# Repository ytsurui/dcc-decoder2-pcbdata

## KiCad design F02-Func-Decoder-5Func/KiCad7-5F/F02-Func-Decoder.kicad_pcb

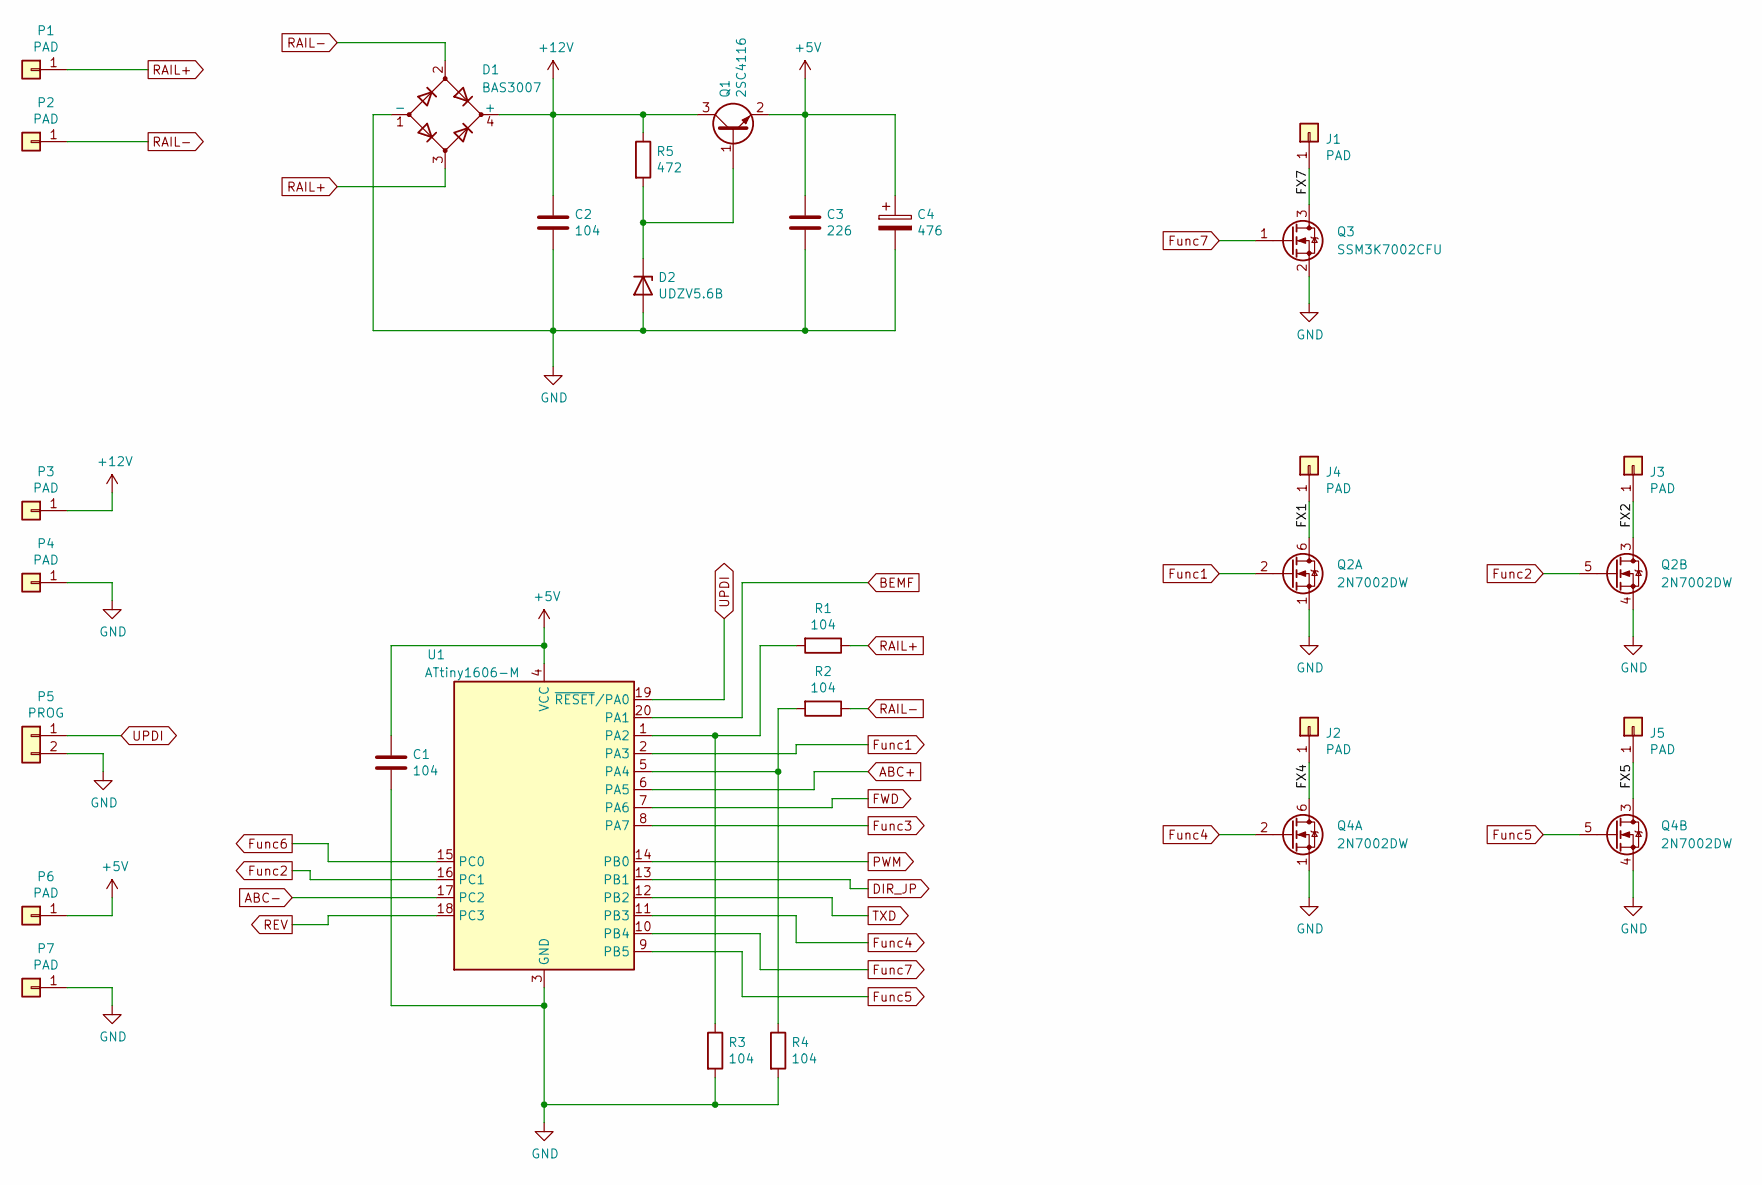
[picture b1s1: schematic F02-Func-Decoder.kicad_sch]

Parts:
C1, C2: 104; C_1005_v2
C3: 226; C_1608
C4: 476; CP_1608
D1: BAS3007; SOT-143
D2: UDZV5.6B; UMD2
J1, J2, J3, J4, J5: PAD; PAD_1.3x1.3_Hole0.9
P1, P2, P3, P4, P6, P7: PAD; PAD_1.3x1.3_Hole0.9
P5: PROG; PAD_PROG_2PIN_HOLE0.7
Q1: 2SC4116; SOT-23
Q2, Q4: 2N7002DW; SOT-363-nomark-v2
Q3: SSM3K7002CFU; SOT-23
R1, R2, R3, R4: 104; R_1608_20240411
R5: 472; R_1608_20240411
U1: ATtiny1606-M; VQFN-20-1EP_3x3mm_P0.4mm_EP1.7x1.7mm

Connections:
+5V: C1.1, C3.1, C4.1, P6.1, Q1.2 (E), U1.4 (VCC)
+12V: C2.1, D1.4 (+), P3.1, Q1.3 (C), R5.1
/FX1: J4.1, Q2.6 (D)
/FX2: J3.1, Q2.3 (D)
/FX4: J2.1, Q4.6 (D)
/FX5: J5.1, Q4.3 (D)
/FX7: J1.1, Q3.3 (D)
ABC+: U1.6 (PA5)
ABC-: U1.17 (PC2)
BEMF: U1.20 (PA1)
DIR_JP: U1.13 (PB1)
FWD: U1.7 (PA6)
Func1: Q2.2 (G), U1.2 (PA3)
Func2: Q2.5 (G), U1.16 (PC1)
Func3: U1.8 (PA7)
Func4: Q4.2 (G), U1.11 (PB3)
Func5: Q4.5 (G), U1.9 (PB5)
Func6: U1.15 (PC0)
Func7: Q3.1 (G), U1.10 (PB4)
GND: C1.2, C2.2, C3.2, C4.2, D1.1 (-), D2.2 (A), P4.1, P5.2, P7.1, Q2.1 (S), Q2.4 (S), Q3.2 (S), Q4.1 (S), Q4.4 (S), R3.2, R4.2, U1.3 (GND), U1.21 (GND)
unnamed: D2.1 (K), Q1.1 (B), R5.2
unnamed: R1.2, R3.1, U1.1 (PA2)
unnamed: R2.2, R4.1, U1.5 (PA4)
PWM: U1.14 (PB0)
RAIL+: D1.3, P1.1, R1.1
RAIL-: D1.2, P2.1, R2.1
REV: U1.18 (PC3)
TXD: U1.12 (PB2)
UPDI: P5.1, U1.19 (~RESET/PA0)

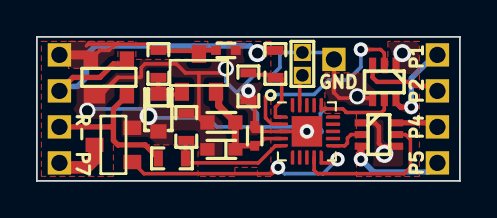
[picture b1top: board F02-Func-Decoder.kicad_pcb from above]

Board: 2 copper layers, 23.5 x 8.0 mm, 26 parts (0 on the bottom side), 19 nets.

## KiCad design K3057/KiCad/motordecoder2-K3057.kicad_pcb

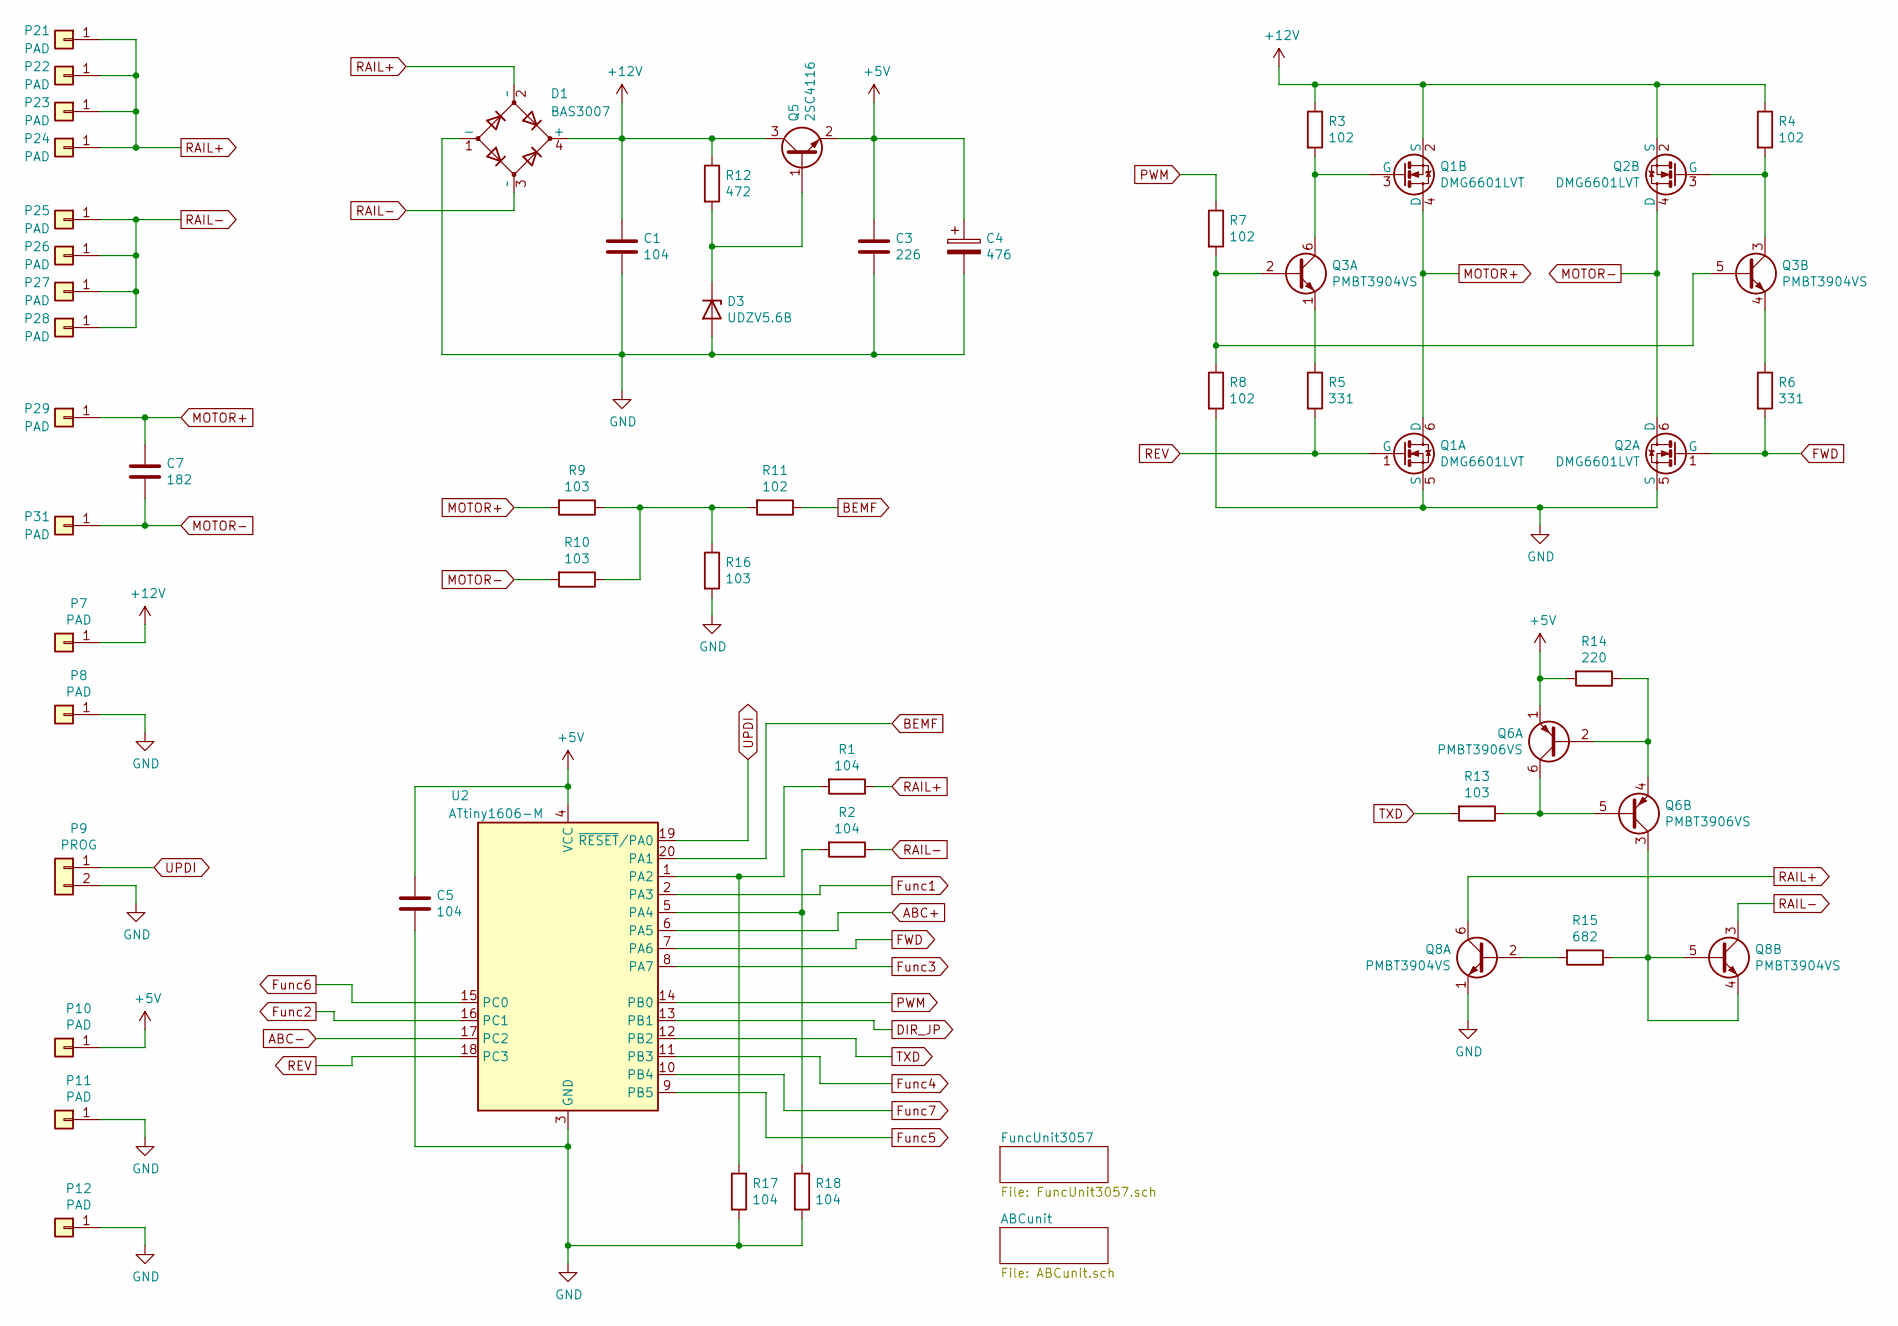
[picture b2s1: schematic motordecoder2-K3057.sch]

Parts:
C1, C5: 104; C_1005_v2
C3: 226; C_1608
C4: 476; CP_1608
C7: 182; C_1005_v2
D1: BAS3007; SOT-143
D3: UDZV5.6B; UMD2
P7: PAD; PAD_1.0x1.8_SMD
P8, P10: PAD; PAD_0.6x1.0_SMD
P9: PROG; PAD_PROG_2PIN_HOLE0.7
P11: PAD; PAD_0.5x1.2_SMD
P12: PAD; PAD_1.0x1.4_SMD
P21, P24, P25, P28, P29, P31: PAD; KATO_RAILPAD_3057_8mm
P22, P23, P26, P27: PAD; KATO_RAILPAD_3057_7mm
Q1, Q2: DMG6601LVT; SOT-23-6
Q3, Q8: PMBT3904VS; SOT-666-nomark
Q5: 2SC4116; SC-70_v2
Q6: PMBT3906VS; SOT-666-nomark
R1, R2, R17, R18: 104; R_1005
R3, R4: 102; R_1608_v2
R5, R6: 331; R_1608_v2
R7, R8, R11: 102; R_1005
R9, R10, R13, R16: 103; R_1005
R12: 472; R_1005
R14: 220; R_1608_v2
R15: 682; R_1005
U2: ATtiny1606-M; VQFN-20-1EP_3x3mm_P0.4mm_EP1.7x1.7mm

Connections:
+5V: C3.1, C4.1, C5.1, P10.1, Q5.2 (E), Q6.1 (E1), R14.2, U2.4 (VCC)
+12V: C1.1, D1.4 (+), P7.1, Q1.2 (S), Q2.2 (S), Q5.3 (C), R3.1, R4.1, R12.1; also elsewhere on the board
ABC+: U2.6 (PA5); also elsewhere on the board
ABC-: U2.17 (PC2); also elsewhere on the board
BEMF: R11.1, U2.20 (PA1)
DIR_JP: U2.13 (PB1); also elsewhere on the board
FWD: Q2.1 (G), R6.2, U2.7 (PA6)
Func1: U2.2 (PA3); also elsewhere on the board
Func2: U2.16 (PC1); also elsewhere on the board
Func3: U2.8 (PA7); also elsewhere on the board
Func4: U2.11 (PB3); also elsewhere on the board
Func5: U2.9 (PB5); also elsewhere on the board
Func6: U2.15 (PC0); also elsewhere on the board
Func7: U2.10 (PB4); also elsewhere on the board
GND: C1.2, C3.2, C4.2, C5.2, D1.1 (-), D3.2 (A), P8.1, P9.2, P11.1, P12.1, Q1.5 (S), Q2.5 (S), Q8.1 (E1), R8.2, R16.2, R17.2, R18.2, U2.3 (GND), U2.21 (GND); also elsewhere on the board
MOTOR+: C7.1, P29.1, Q1.4 (D), Q1.6 (D), R9.2
MOTOR-: C7.2, P31.1, Q2.4 (D), Q2.6 (D), R10.2
unnamed: D3.1 (K), Q5.1 (B), R12.2
unnamed: Q1.3 (G), Q3.6 (C1), R3.2
unnamed: Q2.3 (G), Q3.3 (C2), R4.2
unnamed: Q3.1 (E1), R5.1
unnamed: Q3.2 (B1), Q3.5 (B2), R7.2, R8.1
unnamed: Q3.4 (E2), R6.1
unnamed: Q6.2 (B1), Q6.4 (E2), R14.1
unnamed: Q6.3 (C2), Q8.4 (E2), Q8.5 (B2), R15.1
unnamed: Q6.5 (B2), Q6.6 (C1), R13.1
unnamed: Q8.2 (B1), R15.2
unnamed: R1.2, R17.1, U2.1 (PA2)
unnamed: R9.1, R10.1, R11.2, R16.1
unnamed: R2.2, R18.1, U2.5 (PA4)
PWM: R7.1, U2.14 (PB0)
RAIL+: D1.2 (~~), P21.1, P22.1, P23.1, P24.1, Q8.6 (C1), R1.1; also elsewhere on the board
RAIL-: D1.3 (~~), P25.1, P26.1, P27.1, P28.1, Q8.3 (C2), R2.1; also elsewhere on the board
REV: Q1.1 (G), R5.2, U2.18 (PC3)
TXD: R13.2, U2.12 (PB2)
UPDI: P9.1, U2.19 (~RESET~/PA0)

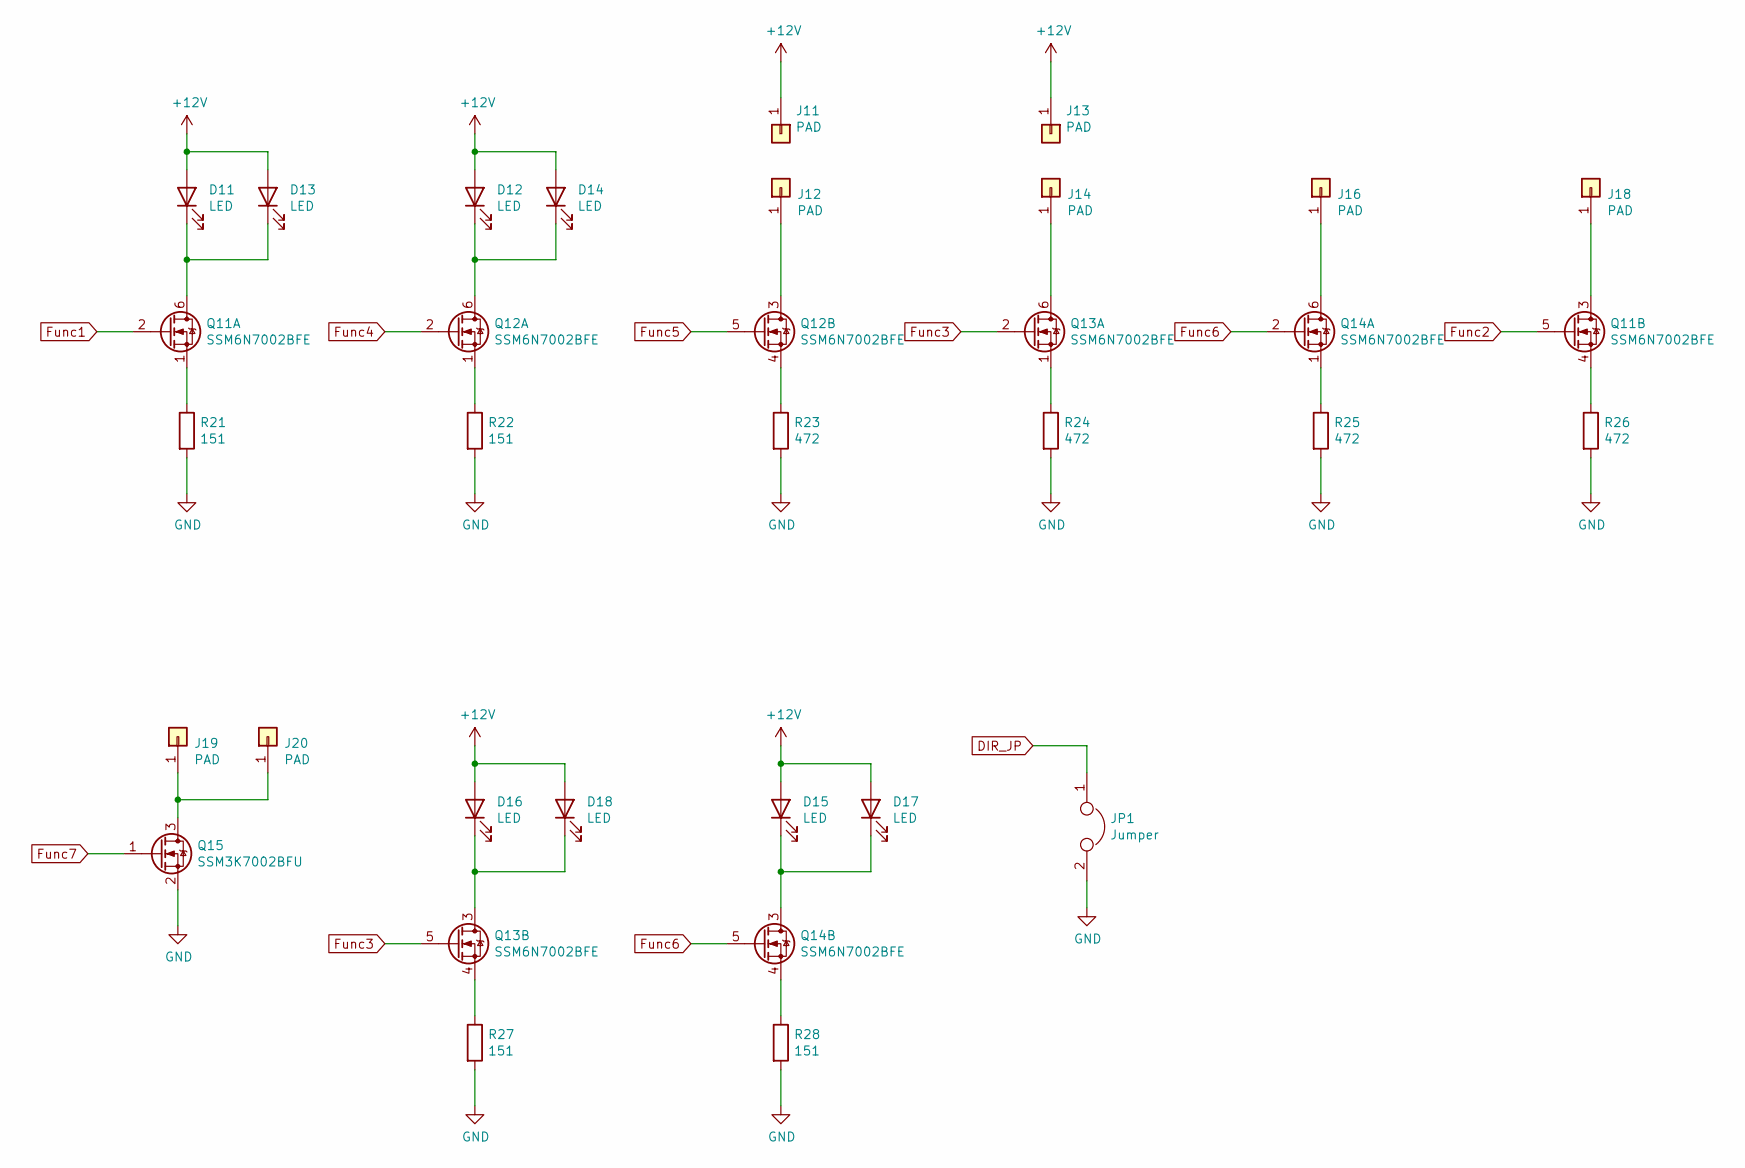
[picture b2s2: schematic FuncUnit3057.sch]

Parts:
D11, D12, D13, D14, D15, D16, D17, D18: LED; LED_1224_1005_SIDE_BIG2
J11, J13: PAD; PAD_1.0x1.8_SMD
J12, J14, J16, J18: PAD; PAD_1.0x1.0_Hole0.6
J19: PAD; PAD_1.0x1.4_SMD
J20: PAD; PAD_0.5x1.2_SMD
JP1: Jumper; SOLDER_CONN_PAD_0.7mm_1.4mm
Q11, Q12, Q13, Q14: SSM6N7002BFE; SOT-666-nomark
Q15: SSM3K7002BFU; SC-70_v2
R21, R22, R27, R28: 151; R_1608_v2
R23, R24, R25, R26: 472; R_1005

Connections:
+12V: D11.2 (A), D12.2 (A), D13.2 (A), D14.2 (A), D15.2 (A), D16.2 (A), D17.2 (A), D18.2 (A), J11.1, J13.1; also elsewhere on the board
DIR_JP: JP1.1; also elsewhere on the board
Func1: Q11.2 (G); also elsewhere on the board
Func2: Q11.5 (G); also elsewhere on the board
Func3: Q13.2 (G), Q13.5 (G); also elsewhere on the board
Func4: Q12.2 (G); also elsewhere on the board
Func5: Q12.5 (G); also elsewhere on the board
Func6: Q14.2 (G), Q14.5 (G); also elsewhere on the board
Func7: Q15.1 (G); also elsewhere on the board
GND: JP1.2, Q15.2 (S), R21.2, R22.2, R23.2, R24.2, R25.2, R26.2, R27.2, R28.2; also elsewhere on the board
unnamed: D11.1 (K), D13.1 (K), Q11.6 (D)
unnamed: D12.1 (K), D14.1 (K), Q12.6 (D)
unnamed: D15.1 (K), D17.1 (K), Q14.3 (D)
unnamed: D16.1 (K), D18.1 (K), Q13.3 (D)
unnamed: J12.1, Q12.3 (D)
unnamed: J14.1, Q13.6 (D)
unnamed: J16.1, Q14.6 (D)
unnamed: J18.1, Q11.3 (D)
unnamed: J19.1, J20.1, Q15.3 (D)
unnamed: Q11.1 (S), R21.1
unnamed: Q11.4 (S), R26.1
unnamed: Q12.1 (S), R22.1
unnamed: Q12.4 (S), R23.1
unnamed: Q13.1 (S), R24.1
unnamed: Q13.4 (S), R27.1
unnamed: Q14.1 (S), R25.1
unnamed: Q14.4 (S), R28.1

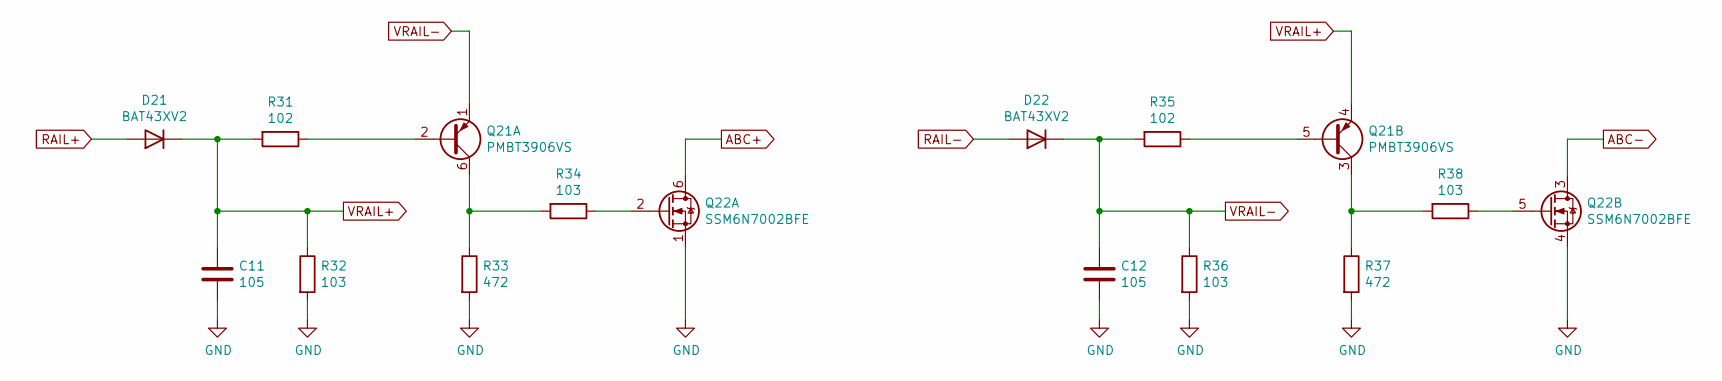
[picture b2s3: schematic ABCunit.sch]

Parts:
C11, C12: 105; C_1005_v2
D21: BAT43XV2; EMD2_small
D22: BAT43XV2; EMD2
Q21: PMBT3906VS; SOT-666-nomark
Q22: SSM6N7002BFE; SOT-666-nomark
R31, R35: 102; R_1005
R32, R34, R36, R38: 103; R_1005
R33, R37: 472; R_1005

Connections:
ABC+: Q22.6 (D); also elsewhere on the board
ABC-: Q22.3 (D); also elsewhere on the board
GND: C11.2, C12.2, Q22.1 (S), Q22.4 (S), R32.2, R33.2, R36.2, R37.2; also elsewhere on the board
unnamed: Q21.2 (B1), R31.1
unnamed: Q21.3 (C2), R37.1, R38.2
unnamed: Q21.5 (B2), R35.1
unnamed: Q21.6 (C1), R33.1, R34.2
unnamed: Q22.2 (G), R34.1
unnamed: Q22.5 (G), R38.1
RAIL+: D21.2 (A); also elsewhere on the board
RAIL-: D22.2 (A); also elsewhere on the board
VRAIL+: C11.1, D21.1 (K), Q21.4 (E2), R31.2, R32.1
VRAIL-: C12.1, D22.1 (K), Q21.1 (E1), R35.2, R36.1

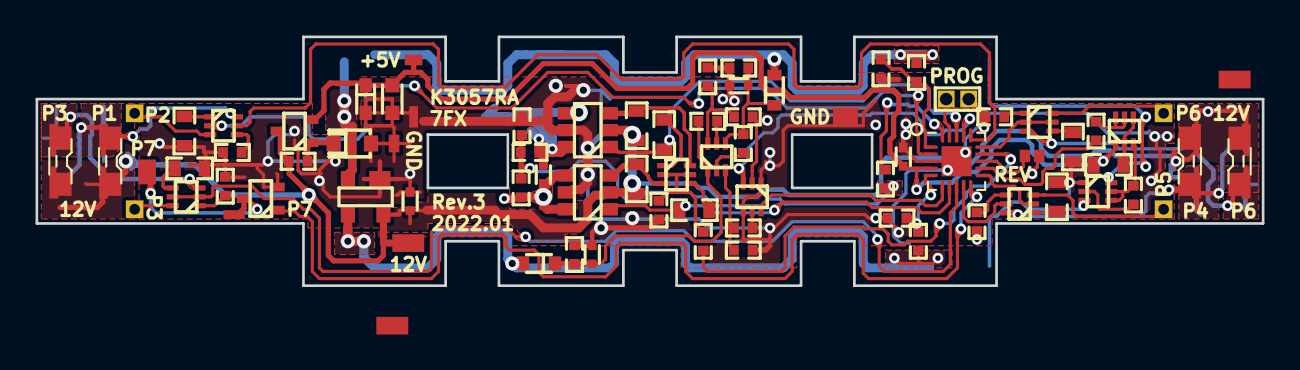
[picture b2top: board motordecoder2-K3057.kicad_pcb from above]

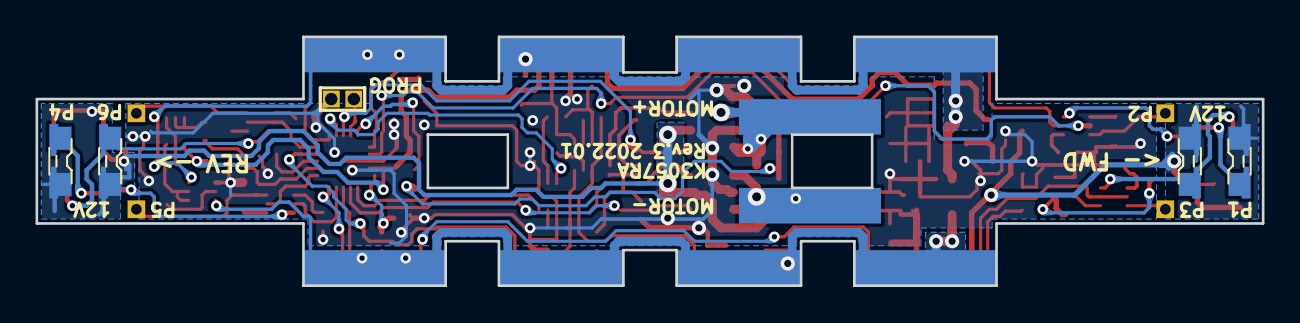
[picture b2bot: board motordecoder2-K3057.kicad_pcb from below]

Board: 2 copper layers, 69.0 x 14.0 mm, 92 parts (4 on the bottom side), 61 nets.
